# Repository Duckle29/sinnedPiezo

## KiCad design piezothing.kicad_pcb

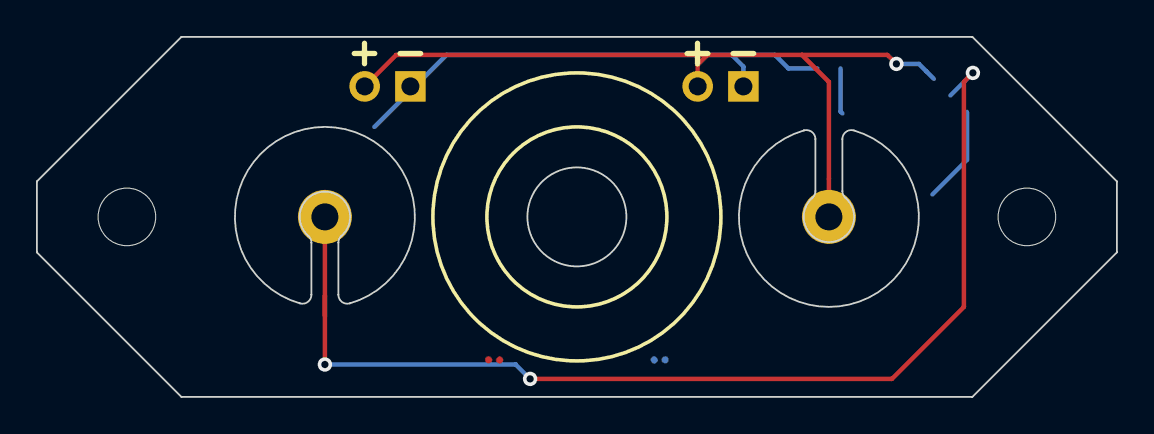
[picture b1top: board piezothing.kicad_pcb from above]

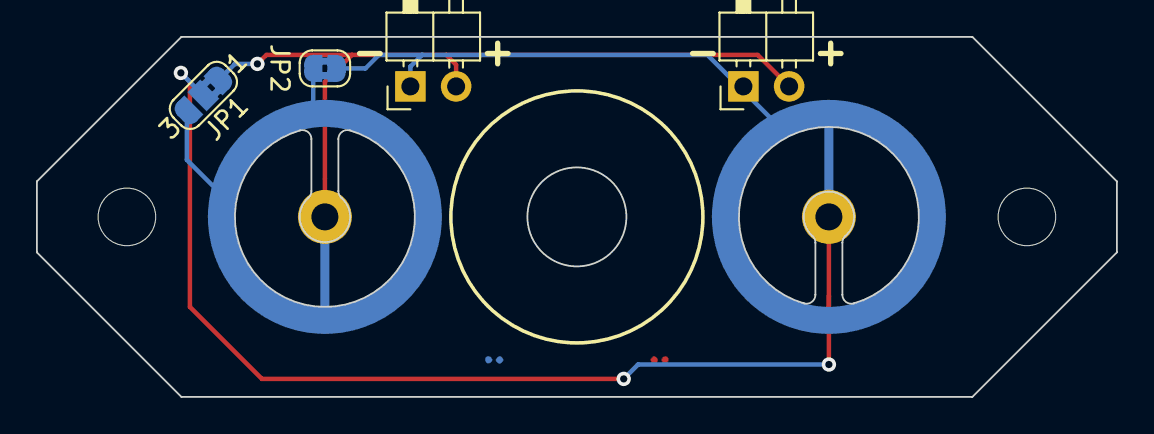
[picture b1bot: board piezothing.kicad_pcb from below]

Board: 2 copper layers, 60.0 x 20.0 mm, 4 parts (4 on the bottom side), 3 nets.

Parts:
J1, J1#2: con; PinHeader_1x02_P2.54mm_Horizontal
JP1: SolderJumper_3_Bridged12; SolderJumper-3_P1.3mm_Bridged2Bar12_RoundedPad1.0x1.5mm_Num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
JP2: SolderJumper_2_Bridged; SolderJumper-2_P1.3mm_Bridged2Bar_RoundedPad1.0x1.5mm

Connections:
/A2: J1.2, J1#2.2, JP1.1
/K1: J1.1, J1#2.1, JP2.1
/K2: JP1.3, JP2.2

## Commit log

2019-03-02 Added second connector, fixed ring short
